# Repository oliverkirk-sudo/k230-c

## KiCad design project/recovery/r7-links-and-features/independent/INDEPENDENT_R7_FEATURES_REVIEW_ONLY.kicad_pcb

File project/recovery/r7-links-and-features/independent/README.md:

# R7 independent audit

2026-10-03. **Pass for the bounded identity/geometry and fabricated-feature change, with the assembly-stencil gate below remaining open.** No application, factory, thermal, lifetime, boot, routed-board or production qualification follows.

The audit compares the published R6 project with the R7 candidate. Main CAD was read-only; checked schematic, PCB, footprint, symbol and project-file hashes were unchanged by this audit. Native tests used KiCad 9.0.2 and separate input copies and output fixtures.

## Exact schematic delta

Fresh native netlist exports and an independent structural comparison of every active schematic confirmed:

- All 254 component values and all 1509 pin/net/function/type bindings are unchanged across 457 nets
- Exactly ten footprint fields changed: R205, R206, R220, R221, R401, R528, R561, JP1, TP81 and TP82
- Exactly three BOM flags changed from included to excluded: JP1, TP81 and TP82
- All on-board flags and DNP states are unchanged; JP1, R45, R47 and R528 remain DNP
- The root schematic's revision label changed from RCV-R6 to RCV-R7; this is the sole additional schematic metadata delta
- Assigned-reference coverage rises from 192/254 to 202/254, leaving 52 unassigned

The full schematic comparison normalized only those explicit fields and that one revision label. Everything else had to match. It did not rely on the implementation's assignment file to establish the changed-reference set. Fresh R7 ERC reports zero violations. See [independent-review.json](independent-review.json), [input-sha256.json](input-sha256.json), [r6-fresh.xml](r6-fresh.xml) and [r7-fresh.xml](r7-fresh.xml).

## Native land and feature checks

The actual library files were resolved from R7's footprint table and loaded with KiCad. The seven passive references retain their original value strings and the source-backed copper:

| Reference | Each pad x × y, mm | Pad center x, mm | Inner gap, mm |
|---|---:|---:|---:|
| R205/R206, existing TNPW | 0.55 × 0.60 | ±0.475 | 0.40 |
| R220, new WSL0603…9 | 1.01 × 1.01 | ±0.755 | 0.50 |
| R561, new WFZ0402 | 0.50 × 0.60 | ±0.450 | 0.40 |
| R221/R401/R528, existing CRCW | 0.28 × 0.43 | ±0.255 | 0.23 |

WSL's 1.80 × 1.02 mm fabrication body envelope conservatively contains the source's 1.774 × 1.014 mm maximum body; its courtyard is 3.12 × 1.62 mm. WFZ's body envelope is 1.10 × 0.60 mm and its courtyard is 2.00 × 1.20 mm. Both use 0.05 mm mask expansion and separate 1:1 paste apertures. These are explicit process candidates; the courtyards are project constructions, not manufacturer approval. Copper agrees with the earlier drawing review of [Vishay WSL p2](https://www.vishay.com/docs/30192/wsl-9.pdf), [WFZ p2](https://www.vishay.com/docs/30432/wfz-jumper.pdf), [TNPW source lands p1](https://www.vishay.com/doc?28950) and [CRCW p2](https://www.vishay.com/docs/20052/crcw0201e3.pdf).

JP1 has two 0.70 × 1.00 mm top pads at x = ±0.50 mm, leaving a 0.30 mm copper gap. There is no connecting copper, paste, track or zone in its definition. It remains DNP/open. Its pad nets remain MODE_TF and VDD_3V3. TP81/TP82 each have one circular 0.80 mm bare top pad, no paste and no drill, retaining PMU_OUT0_STATUS and PMU_OUT1_STATUS respectively. All three remain schematic-bound, on-board features, excluded from BOM and position files; none is marked BoardOnly.

## Actual copper, paste and placement exports

The independent fixture contains all ten reviewed references, including R528. It uses a deliberately isolated six-layer, 38 × 20 mm test outline with no routing; this is not the 38 × 38 mm module layout. Embedded footprints and copied source definitions are included solely for reproducible inspection.

Default native Gerber exports contain 18 copper flashes, 18 mask flashes and 14 paste flashes. JP1's two copper pads and both test pads remain present. No connecting copper line is emitted. JP1, TP81 and TP82 have no paste apertures.

**R528's two paste apertures remain in KiCad's default F.Paste export even though it is DNP and excluded from placement.** DNP/BOM/position attributes therefore do not establish a safe production stencil. A deliberate assembly/stencil variant, followed by inspection of its generated paste output, is required before manufacturing. The diagnostic Gerbers in this folder must not be released as production outputs.

Both [default placement export](positions_default.csv) and the export with `--exclude-dnp` include exactly R205, R206, R220, R221, R401 and R561. R528 and all three fabricated features are absent. Thus placement exclusion and copper retention work as intended, independently of the still-open stencil decision.

The [native copper preview](copper-review.svg) was inspected. JP1 is visibly open, R528's pads remain and the two test pads are present. The two unlabeled upper-row pairs are R205/R206, whose existing reference fields are on F.Fab rather than F.SilkS.

## Shared population helper

The helper preserves pad positions, sizes and net identities while applying the intended attributes. Independent negative controls rejected BoardOnly on an ordinary resistor and on JP1, removal of position exclusion from R528 or TP81, removal of JP1's DNP state, and reintroduction of TP82 to the BOM. These checks exercise actual native footprint attributes.

Native fixture DRC has zero rule violations and **three expected unrouted connections** on its retained shared nets: VDD_3V3, GND and VDD1P8. These are explicitly reported in [fixture-drc.json](fixture-drc.json); this is not a connected or fabrication-ready circuit. [native-checks.json](native-checks.json) records the commands and results.

## Remaining limits and reproduction

The previous precision/lifetime, hot-resistance/current, R401 firmware/input, R221 branch-current and R528 boot-voltage gates remain open. Assigning these footprints does not resolve them. The mechanical body/courtyard checks establish the geometry represented in this candidate, not top-side fit, escape routing, solder-process acceptance or six-layer production feasibility.

[validate_independent.py](validate_independent.py) accepts explicit `--baseline`, `--project`, `--output` and `--runtime` paths. Run it with the system Python that provides pcbnew. It copies input CAD into the runtime location, exports fresh netlists, checks the allowed deltas, loads native footprints, exercises population controls and creates the diagnostic fixture/exports. Its generated outputs belong in an audit directory, never the active board or manufacturing package.

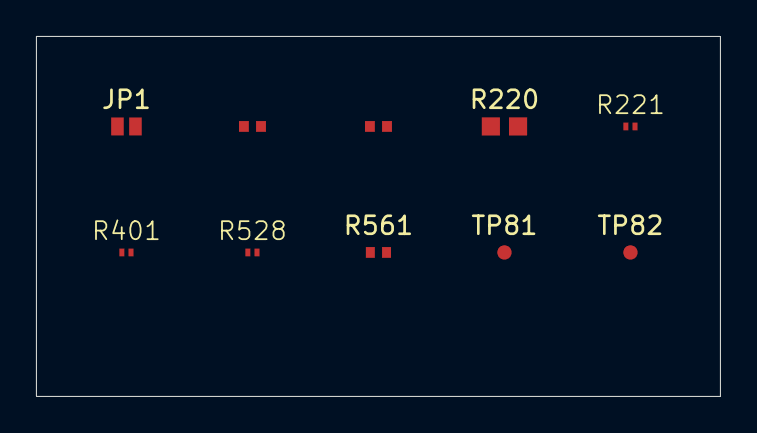
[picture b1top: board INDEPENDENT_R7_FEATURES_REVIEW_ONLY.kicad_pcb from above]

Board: 6 copper layers, 38.0 x 20.0 mm, 10 parts (0 on the bottom side), 3 nets, no tracks yet.

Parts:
JP1: OPEN=EMMC / CLOSED=TF; COLD ONLY; Core_Cold_Selector_Open_SolderBridge_CANDIDATE
R205, R206: 56.2k 1% / 0.8V / addr0x49; Vishay_TNPW0402_IPC7351_SourceLand_PROCESS_CANDIDATE
R220: 0R WSL060300000ZEA9 Rmax=0.25mOhm; Vishay_WSL0603_9_SourceLand_PROCESS_CANDIDATE
R221: 0R Rmax<=50mOhm; Vishay_CRCW0201_SourceLand_PROCESS_CANDIDATE
R401: 0R PMU AUTO-START STRAP; Vishay_CRCW0201_SourceLand_PROCESS_CANDIDATE
R528: 0R QUALIFICATION STRAP DNP; Vishay_CRCW0201_SourceLand_PROCESS_CANDIDATE
R561: 0R WFZ040200000ZE66 3mOhm CANDIDATE; Vishay_WFZ0402_SourceLand_PROCESS_CANDIDATE
TP81: PMU OUT0 OBSERVE ONLY; Core_PMUSTATUS_Top_TestPad_0p8_CANDIDATE
TP82: PMU OUT1 OBSERVE ONLY; Core_PMUSTATUS_Top_TestPad_0p8_CANDIDATE

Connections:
GND: R205.2, R206.2
VDD1P8: R528.1, R561.1
VDD_3V3: JP1.2, R221.1
